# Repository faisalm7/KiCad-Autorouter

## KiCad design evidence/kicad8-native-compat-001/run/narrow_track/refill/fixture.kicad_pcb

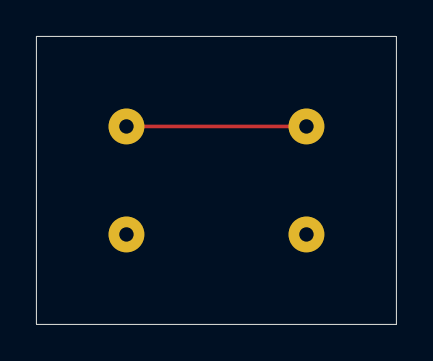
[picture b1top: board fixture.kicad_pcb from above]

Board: 2 copper layers, 20.0 x 16.0 mm, 4 parts (0 on the bottom side), 2 nets.

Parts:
J1, J2, J3, J4: owned_compat_terminal

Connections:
GND: J3.1, J4.1
SIGNAL: J1.1, J2.1

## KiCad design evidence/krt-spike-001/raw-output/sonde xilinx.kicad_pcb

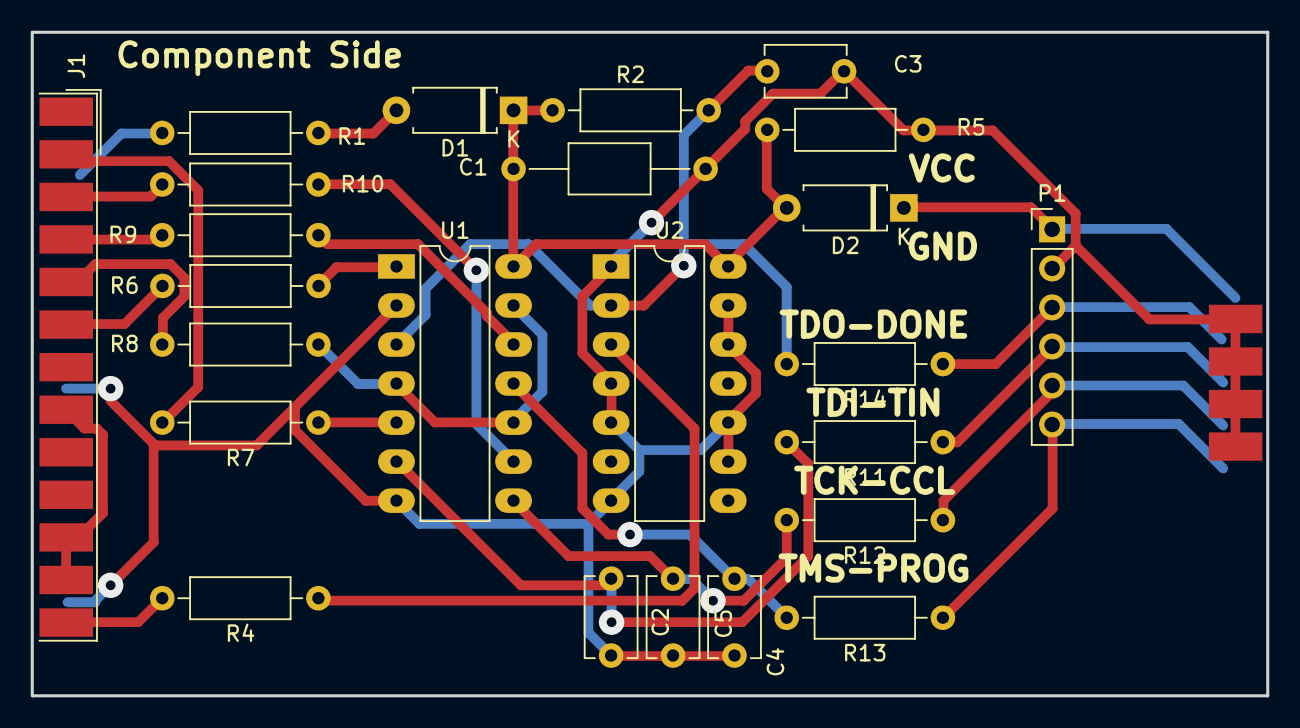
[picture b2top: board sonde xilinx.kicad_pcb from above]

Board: 2 copper layers, 80.4 x 43.2 mm, 25 parts (1 on the bottom side), 26 nets.

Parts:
C1: 1uF; C_Axial_L5.1mm_D3.1mm_P12.50mm_Horizontal
C2, C3, C4, C5: 100pF; C_Disc_D5.1mm_W3.2mm_P5.00mm
D1, D2: BAT46; D_A-405_P7.62mm_Horizontal
J1: DB25MALE; DSUB-25_Male_EdgeMount_P2.77mm
J2: DB9MALE; DSUB-9_Male_EdgeMount_P2.77mm
P1: CONN_6; PinHeader_1x06_P2.54mm_Vertical
R1, R6, R7, R8, R9, R10, R11, R12, R13, R14: 100; R_Axial_DIN0207_L6.3mm_D2.5mm_P10.16mm_Horizontal
R2: 5,1K; R_Axial_DIN0207_L6.3mm_D2.5mm_P10.16mm_Horizontal
R4: 47; R_Axial_DIN0207_L6.3mm_D2.5mm_P10.16mm_Horizontal
R5: 1K; R_Axial_DIN0207_L6.3mm_D2.5mm_P10.16mm_Horizontal
U1, U2: 74LS125; DIP-14_W7.62mm_LongPads

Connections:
/CLK-D1: J1.3, R10.2
/CTRL-D3: J1.5, R8.2
/DONE-SELECT*: J1.13, R4.2
/PWR_3,3-5V: D2.1 (A), J2.1, P1.1
/TCK-CCLK: J2.4, P1.5, R12.1
/TD0-DONE: J2.2, P1.3, R14.1
/TD0-PROG-D4: J1.6, R6.2
/TDI-DIN: J2.3, P1.4, R11.1
/TDI-DIN-D0: J1.2, R7.2
/TMS-PROG: J2.5, P1.6, R13.1
/TMS-PROG-D2: J1.4, R9.2
/VCC_SENSE-ERROR*: J1.15, R1.2
GND: C1.2, C2.2, C3.2, C4.2, C5.2, J1.20, J1.25, J2.6, J2.7, J2.8, J2.9, P1.2, R5.2, U1.2 (D), U1.7 (GND), U2.1 (E), U2.4 (E), U2.5 (D), U2.7 (GND), U2.9 (D), U2.10 (E), U2.12 (D), U2.13 (E)
unnamed: D1.2 (K), R1.1
unnamed: J1.8, J1.11, J1.12
unnamed: R6.1, U1.1 (E)
unnamed: C3.1, R2.2, R14.2, U1.3 (O), U2.2 (D)
unnamed: R7.1, U1.5 (D)
unnamed: R8.1, U1.4 (E), U1.10 (E), U1.13 (E)
unnamed: C2.1, R11.2, U1.6 (O)
unnamed: R10.1, U1.9 (D)
unnamed: C5.1, R12.2, U1.8 (O)
unnamed: R9.1, U1.12 (D)
unnamed: C4.1, R13.2, U1.11 (O)
unnamed: R4.1, U2.3 (O)
VCC: C1.1, D1.1 (A), D2.2 (K), R2.1, R5.1, U1.14 (VCC), U2.14 (VCC)
